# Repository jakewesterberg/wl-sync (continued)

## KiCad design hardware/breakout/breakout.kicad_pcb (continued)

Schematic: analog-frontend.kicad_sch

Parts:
C34, C35, C36, C37, C38, C39, C40, C41, C42, C43, C44, C45, C46, C47, C52, C53, C58, C59, C60, C61, C62, C63, C64, C65, C66, C67, C68, C69, C70, C71: 100nF; C_0603_1608Metric
C48, C50: 22pF; C_0603_1608Metric
C49, C51: 6.8nF; C_0603_1608Metric
C54: 1.2nF; C_0603_1608Metric
C55: 1.0nF; C_0603_1608Metric
C56: 1.5nF; C_0603_1608Metric
C57: 220pF; C_0603_1608Metric
D23, D24, D25, D26, D27, D28, D29, D30, D31, D32, D33, D34, D35, D36, D37, D38: BAT54S; SOT-23
J19: ACCES I/O USB-AO16-8A mating DB37 -- six eye chan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; DSUB-37_Pins_Horizontal_P2.77x2.84mm_EdgePinOffset9.90mm_Ho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
J20: Dual panel BNC: Photodiode 1 (passive, coax, phot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; BNC_Dual_RA_Isolated
J22: Dual panel BNC: Microphone (battery-powered, in b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; BNC_Dual_RA_Isolated
J24: Dual panel BNC: Accelerometer motion energy (batt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; BNC_Dual_RA_Isolated
J26: Dual panel BNC: Joystick Y (battery-powered, in b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; BNC_Dual_RA_Isolated
J28: Misc analog input 1 (panel BNC, /1//2 selectable)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; PinHeader_2x03_P2.54mm_Vertical
J29: Dual panel BNC: Misc analog input 2 (panel BNC, /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; BNC_Dual_RA_Isolated
J30: Misc analog input 2 (panel BNC, /1//2 selectable)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; PinHeader_2x03_P2.54mm_Vertical
J32: Misc analog input 3 (panel BNC, /1//2 selectable)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; PinHeader_2x03_P2.54mm_Vertical
R27, R35, R37, R43, R53, R55, R57, R59, R61, R67, R73: 10; R_0603_1608Metric
R28, R29, R30, R31, R32, R33, R34, R36, R42, R52, R54, R56, R58, R60, R66, R72: 1k; R_0603_1608Metric
R38, R40: 180k; R_0603_1608Metric
R39, R41: 1.6k; R_0603_1608Metric
R44, R45, R46, R47, R62, R63, R64, R65, R68, R69, R70, R71, R74, R75, R76, R77: 10.0k 0.1%; R_0603_1608Metric
R48, R49: 12.1k; R_0603_1608Metric
R50, R51: 23.2k; R_0603_1608Metric
R196, R197: DNP; R_0603_1608Metric; not fitted
U16, U17, U18, U19, U20, U21, U24, U25, U26, U27, U28, U29, U30: INA105KU; SOIC-8_3.9x4.9mm_P1.27mm
U22: OPA2197IDR; SOIC-8_3.9x4.9mm_P1.27mm
U23: OPA4197IDR; SOIC-14_3.9x8.7mm_P1.27mm

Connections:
ACCESIO_AGND: J19.1 (AGND), J19.2 (AGND), J19.3 (AGND), J19.4 (AGND), J19.5 (AGND), J19.6 (AGND), J19.7 (AGND), J19.8 (AGND), J19.9 (AGND), J19.10 (AGND), J19.11 (AGND), J19.12 (AGND), J19.13 (AGND), J19.14 (AGND), J19.15 (AGND), J19.16 (AGND), J19.17 (AGND), J19.18 (AGND), J19.19 (AGND), R27.1, U16.2 (-), U17.2 (-), U18.2 (-), U19.2 (-), U20.2 (-), U21.2 (-)
ACCESIO_SHELL: J19.SH; also elsewhere on the board
A_ACC: U25.5 (SENSE), U25.6; also elsewhere on the board
A_ACC_CLAMP: D33.3 (COM), R54.2, U25.3 (+)
A_ACC_RAW: J24.1 (A_In), R54.1
A_ACC_SHLD: J24.2 (A_Ext), R55.1, U25.2 (-)
A_AMB: U24.5 (SENSE), U24.6; also elsewhere on the board
A_AMB_CLAMP: D32.3 (COM), R52.2, U24.3 (+)
A_AMB_RAW: J22.3 (B_In), R52.1
A_AMB_SHLD: J22.4 (B_Ext), R53.1, U24.2 (-)
A_EYE_LP: U20.5 (SENSE), U20.6; also elsewhere on the board
A_EYE_LP_CLAMP: D27.3 (COM), R32.2, U20.3 (+)
A_EYE_LP_DAC: J19.24 (DAC4), R32.1
A_EYE_LX: U16.5 (SENSE), U16.6; also elsewhere on the board
A_EYE_LX_CLAMP: D23.3 (COM), R28.2, U16.3 (+)
A_EYE_LX_DAC: J19.20 (DAC0), R28.1
A_EYE_LY: U17.5 (SENSE), U17.6; also elsewhere on the board
A_EYE_LY_CLAMP: D24.3 (COM), R29.2, U17.3 (+)
A_EYE_LY_DAC: J19.21 (DAC1), R29.1
A_EYE_RP: U21.5 (SENSE), U21.6; also elsewhere on the board
A_EYE_RP_CLAMP: D28.3 (COM), R33.2, U21.3 (+)
A_EYE_RP_DAC: J19.25 (DAC5), R33.1
A_EYE_RX: U18.5 (SENSE), U18.6; also elsewhere on the board
A_EYE_RX_CLAMP: D25.3 (COM), R30.2, U18.3 (+)
A_EYE_RX_DAC: J19.22 (DAC2), R30.1
A_EYE_RY: U19.5 (SENSE), U19.6; also elsewhere on the board
A_EYE_RY_CLAMP: D26.3 (COM), R31.2, U19.3 (+)
A_EYE_RY_DAC: J19.23 (DAC3), R31.1
A_JOY_X: U26.5 (SENSE), U26.6; also elsewhere on the board
A_JOY_X_CLAMP: D34.3 (COM), R56.2, U26.3 (+)
A_JOY_X_RAW: J24.3 (B_In), R56.1
A_JOY_X_SHLD: J24.4 (B_Ext), R57.1, U26.2 (-)
A_JOY_Y: U27.5 (SENSE), U27.6; also elsewhere on the board
A_JOY_Y_CLAMP: D35.3 (COM), R58.2, U27.3 (+)
A_JOY_Y_RAW: J26.1 (A_In), R58.1
A_JOY_Y_SHLD: J26.2 (A_Ext), R59.1, U27.2 (-)
A_MIC: C56.2, U23.8, U23.9 (-); also elsewhere on the board
A_MIC_CLAMP: D31.3 (COM), R42.2, R44.1
A_MIC_DA: R45.2, R48.1, U23.1
A_MIC_DAN: R44.2, R45.1, U23.2 (-)
A_MIC_DAP: R46.2, R47.1, U23.3 (+)
A_MIC_RAW: J22.1 (A_In), R42.1
A_MIC_S1: C54.2, R50.1, U23.6 (-), U23.7
A_MIC_S1_SKN: C54.1, R48.2, R49.1
A_MIC_S1_SKP: C55.1, R49.2, U23.5 (+)
A_MIC_SHLD: J22.2 (A_Ext), R43.1, R46.1
A_MIC_SKN: C56.1, R50.2, R51.1
A_MIC_SKP: C57.1, R51.2, U23.10 (+)
A_MIC_SPARE_FB: U23.13 (-), U23.14
A_MISC1: U28.5 (SENSE), U28.6; also elsewhere on the board
A_MISC1_CLAMP: D36.3 (COM), J28.1, R60.2, R62.1
A_MISC1_DIV: J28.3, U28.3 (+)
A_MISC1_MID: J28.5, R62.2, R63.1
A_MISC1_RAW: J26.3 (B_In), R60.1
A_MISC1_SHLD: J26.4 (B_Ext), J28.2, R61.1, R64.1
A_MISC1_SHLD_DIV: J28.4, U28.2 (-)
A_MISC1_SHLD_MID: J28.6, R64.2, R65.1
A_MISC2: U29.5 (SENSE), U29.6; also elsewhere on the board
A_MISC2_CLAMP: D37.3 (COM), J30.1, R66.2, R68.1
A_MISC2_DIV: J30.3, U29.3 (+)
A_MISC2_MID: J30.5, R68.2, R69.1
A_MISC2_RAW: J29.1 (A_In), R66.1
A_MISC2_SHLD: J29.2 (A_Ext), J30.2, R67.1, R70.1
A_MISC2_SHLD_DIV: J30.4, U29.2 (-)
A_MISC2_SHLD_MID: J30.6, R70.2, R71.1
A_MISC3: U30.5 (SENSE), U30.6; also elsewhere on the board
A_MISC3_CLAMP: D38.3 (COM), J32.1, R72.2, R74.1
A_MISC3_DIV: J32.3, U30.3 (+)
A_MISC3_MID: J32.5, R74.2, R75.1
A_MISC3_RAW: J29.3 (B_In), R72.1
A_MISC3_SHLD: J29.4 (B_Ext), J32.2, R73.1, R76.1
A_MISC3_SHLD_DIV: J32.4, U30.2 (-)
A_MISC3_SHLD_MID: J32.6, R76.2, R77.1
A_PD1: C49.1, R39.2; also elsewhere on the board
A_PD1_CLAMP: C48.2, D29.3 (COM), R34.2, R38.2, R196.2, U22.2 (-)
A_PD1_RAW: J20.1 (A_In), R34.1
A_PD1_RAWOUT: C48.1, R38.1, R39.1, R196.1, U22.1
A_PD1_SHLD: J20.2 (A_Ext), R35.1, U22.3 (+)
A_PD2: C51.1, R41.2; also elsewhere on the board
A_PD2_CLAMP: C50.2, D30.3 (COM), R36.2, R40.2, R197.2, U22.6 (-)
A_PD2_RAW: J20.3 (B_In), R36.1
A_PD2_RAWOUT: C50.1, R40.1, R41.1, R197.1, U22.7
A_PD2_SHLD: J20.4 (B_Ext), R37.1, U22.5 (+)

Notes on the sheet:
Analog front end (Task 10a) -- 16 sources, every one received DIFFERENTIALLY.
Consumes +12V/-12V/AGND (Task 7). Produces the 16 A_* nets below; Tasks 10b/10c/
10d (NI fan-out, mux+Intan diff-amps, comparators) consume them by this same
global-label name -- neither exists yet, but each net's own driving stage
already puts 2 pins on it (SENSE=OUTPUT / filter R+C midpoint / SK follower
feedback), so kicad-cli sch erc's isolated_pin_label check does not fire here
even without a downstream load -- see check_breakout_analog_frontend_netlist.py
and task-10a-report.md for the full ERC accounting.
WHY DIFFERENTIAL (spec Sec.5.6): the rig sits in a Faraday cage sound booth.
Sensors inside are battery powered so no mains conductor crosses the cage wall --
only signal, through a BNC shield. Whether the bulkhead bonds that shield to the
cage shell is UNDECIDED. If it does, circulating current in the shield (which is
also the signal return) would add straight onto the signal through a plain AGND-
referenced buffer. The shield cannot simply be lifted -- it IS the return path.
So every front end senses centre against shield AT THE CONNECTOR and a difference
amplifier turns the disturbance into common mode instead. This is what lets the
bulkhead decision be made, or reversed, later, without touching this board.
The six ACCESIO eye channels get the identical treatment against the ACCESIO's
own AGND pins (bonded to board AGND through ~10R, same as a BNC shell) -- it sits
on a separately-earthed eye-tracker PC, the same class of ground offset.
Common front end, every one of the 16 sources: isolated BNC (or ACCESIO DB37
pin) -> 1k series -> BAT54S clamp to +12V/-12V (protects the receiving op-amp's
own supply rails) -> source-specific back half below.
13 of 16 (6 ACCESIO eyes, ambient, accelerometer, joystick X/Y, misc x3): one
INA105KU per channel -- TI's monolithic precision unity-gain difference
amplifier (matched internal resistor network, REF pin lands the output on AGND
regardless of what the shield/ACCESIO_AGND reference is doing). Named
'INA134-class' in the brief; INA134 itself has no stock KiCad symbol and is an
audio-specific part -- INA105 fills the identical topological role and is a
real, current, hand-solderable TI part (same Value-substitution discipline as
the mule's SN74LVC541APW-on-74LS541-symbol precedent, hardware/README.md).
Photodiodes (A_PD1/A_PD2, spec Sec.6.3.1): PASSIVE, so the input stage is a
transimpedance amplifier, not a difference amp. Photodiode lives at the remote
sensor (not on this board, like the mic/accelerometer/joystick) -- cathode on
the coax centre (TIA summing junction, op-amp '-'), anode on the shield.
Non-inverting input ('+') is referenced to the LOCAL SHIELD, not AGND: feedback
forces the summing junction to track '+', so both photodiode terminals sit at
the shield's own local potential at every instant -- true photovoltaic (zero-
bias) operation survives a shield disturbance instead of that disturbance
appearing as a real bias voltage across the diode.

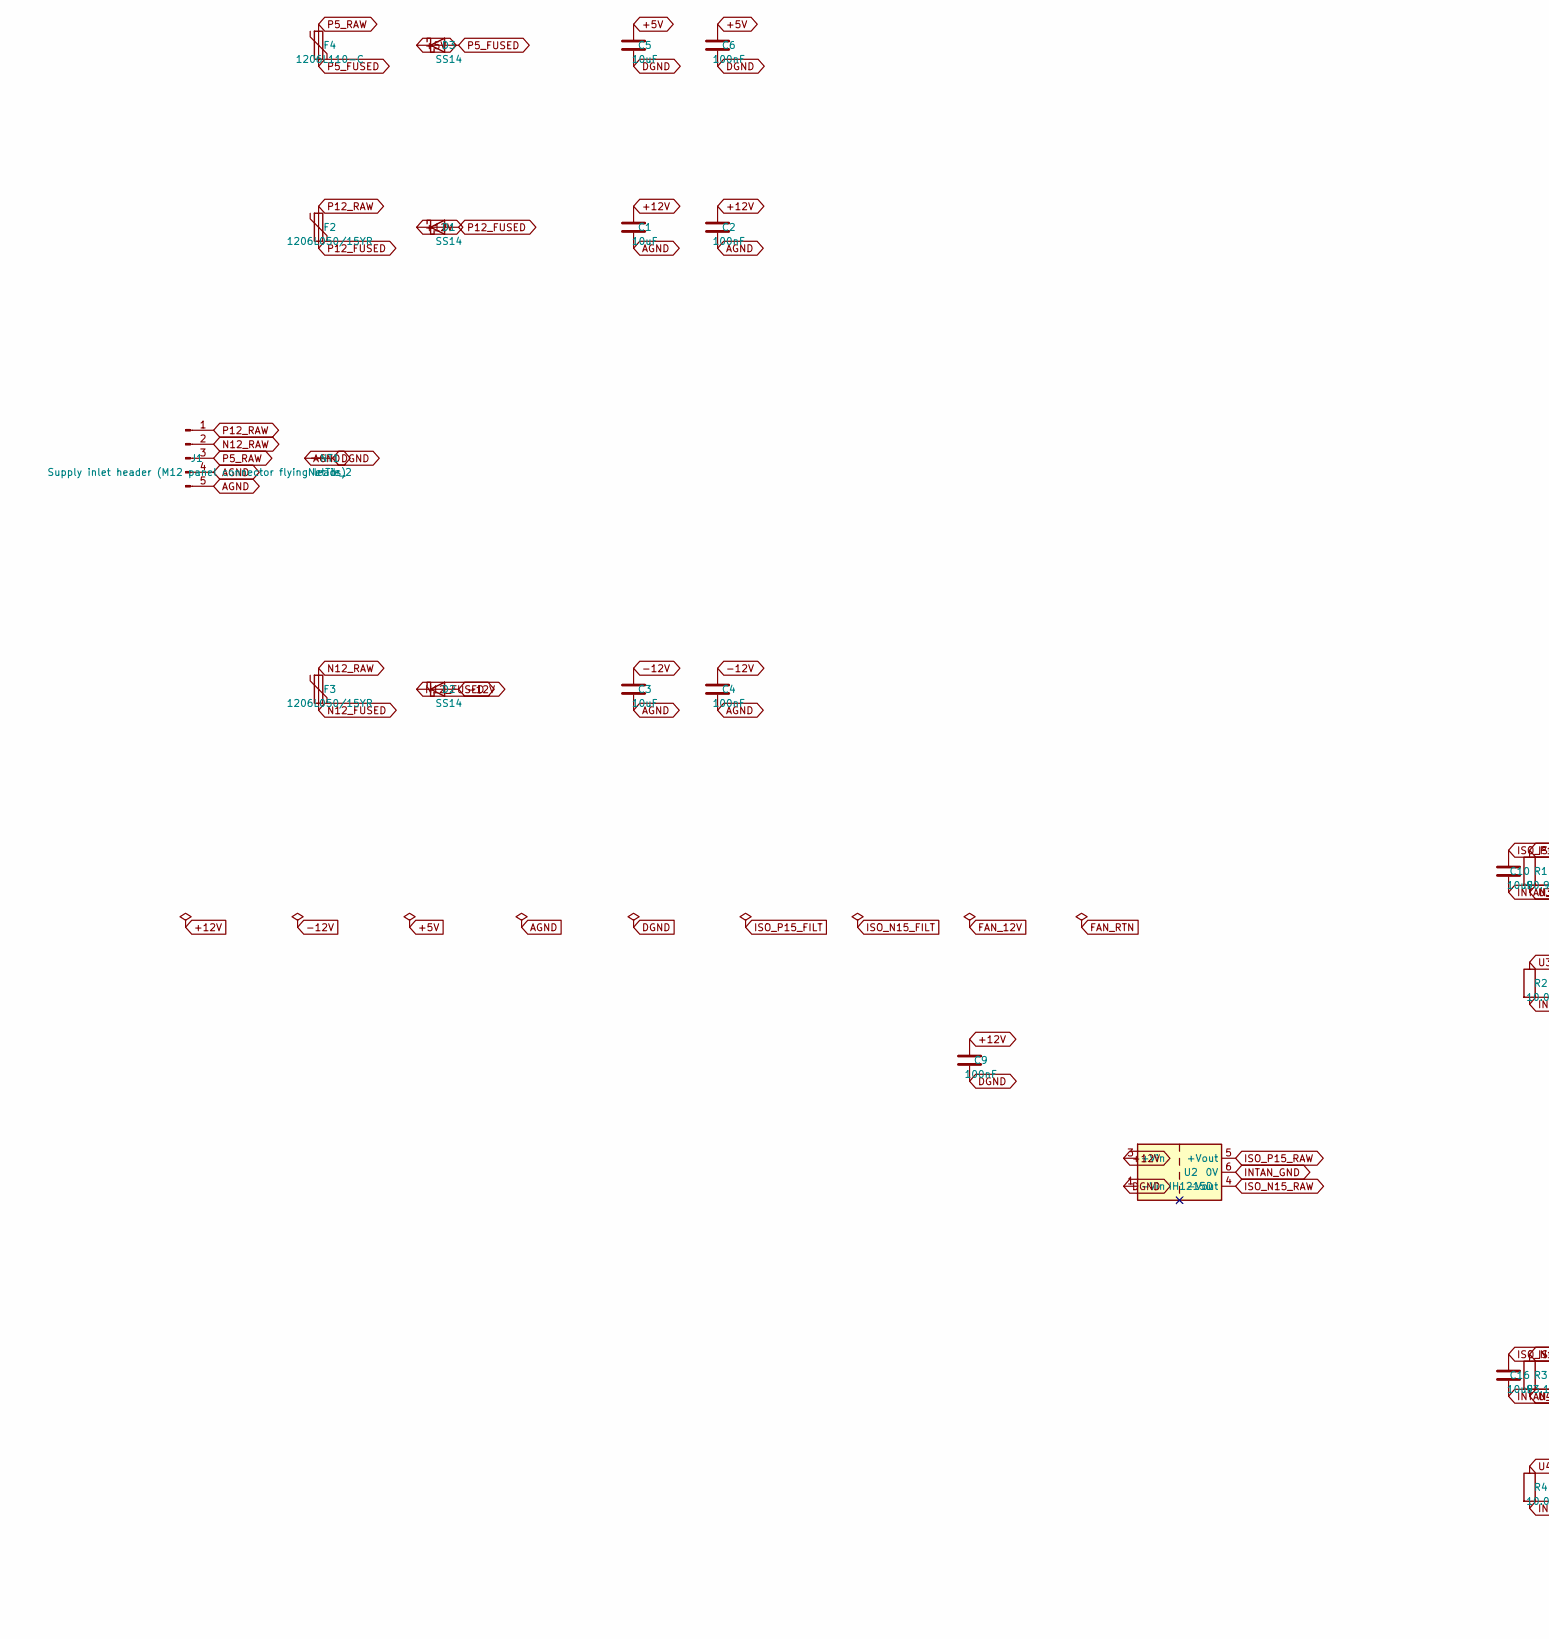
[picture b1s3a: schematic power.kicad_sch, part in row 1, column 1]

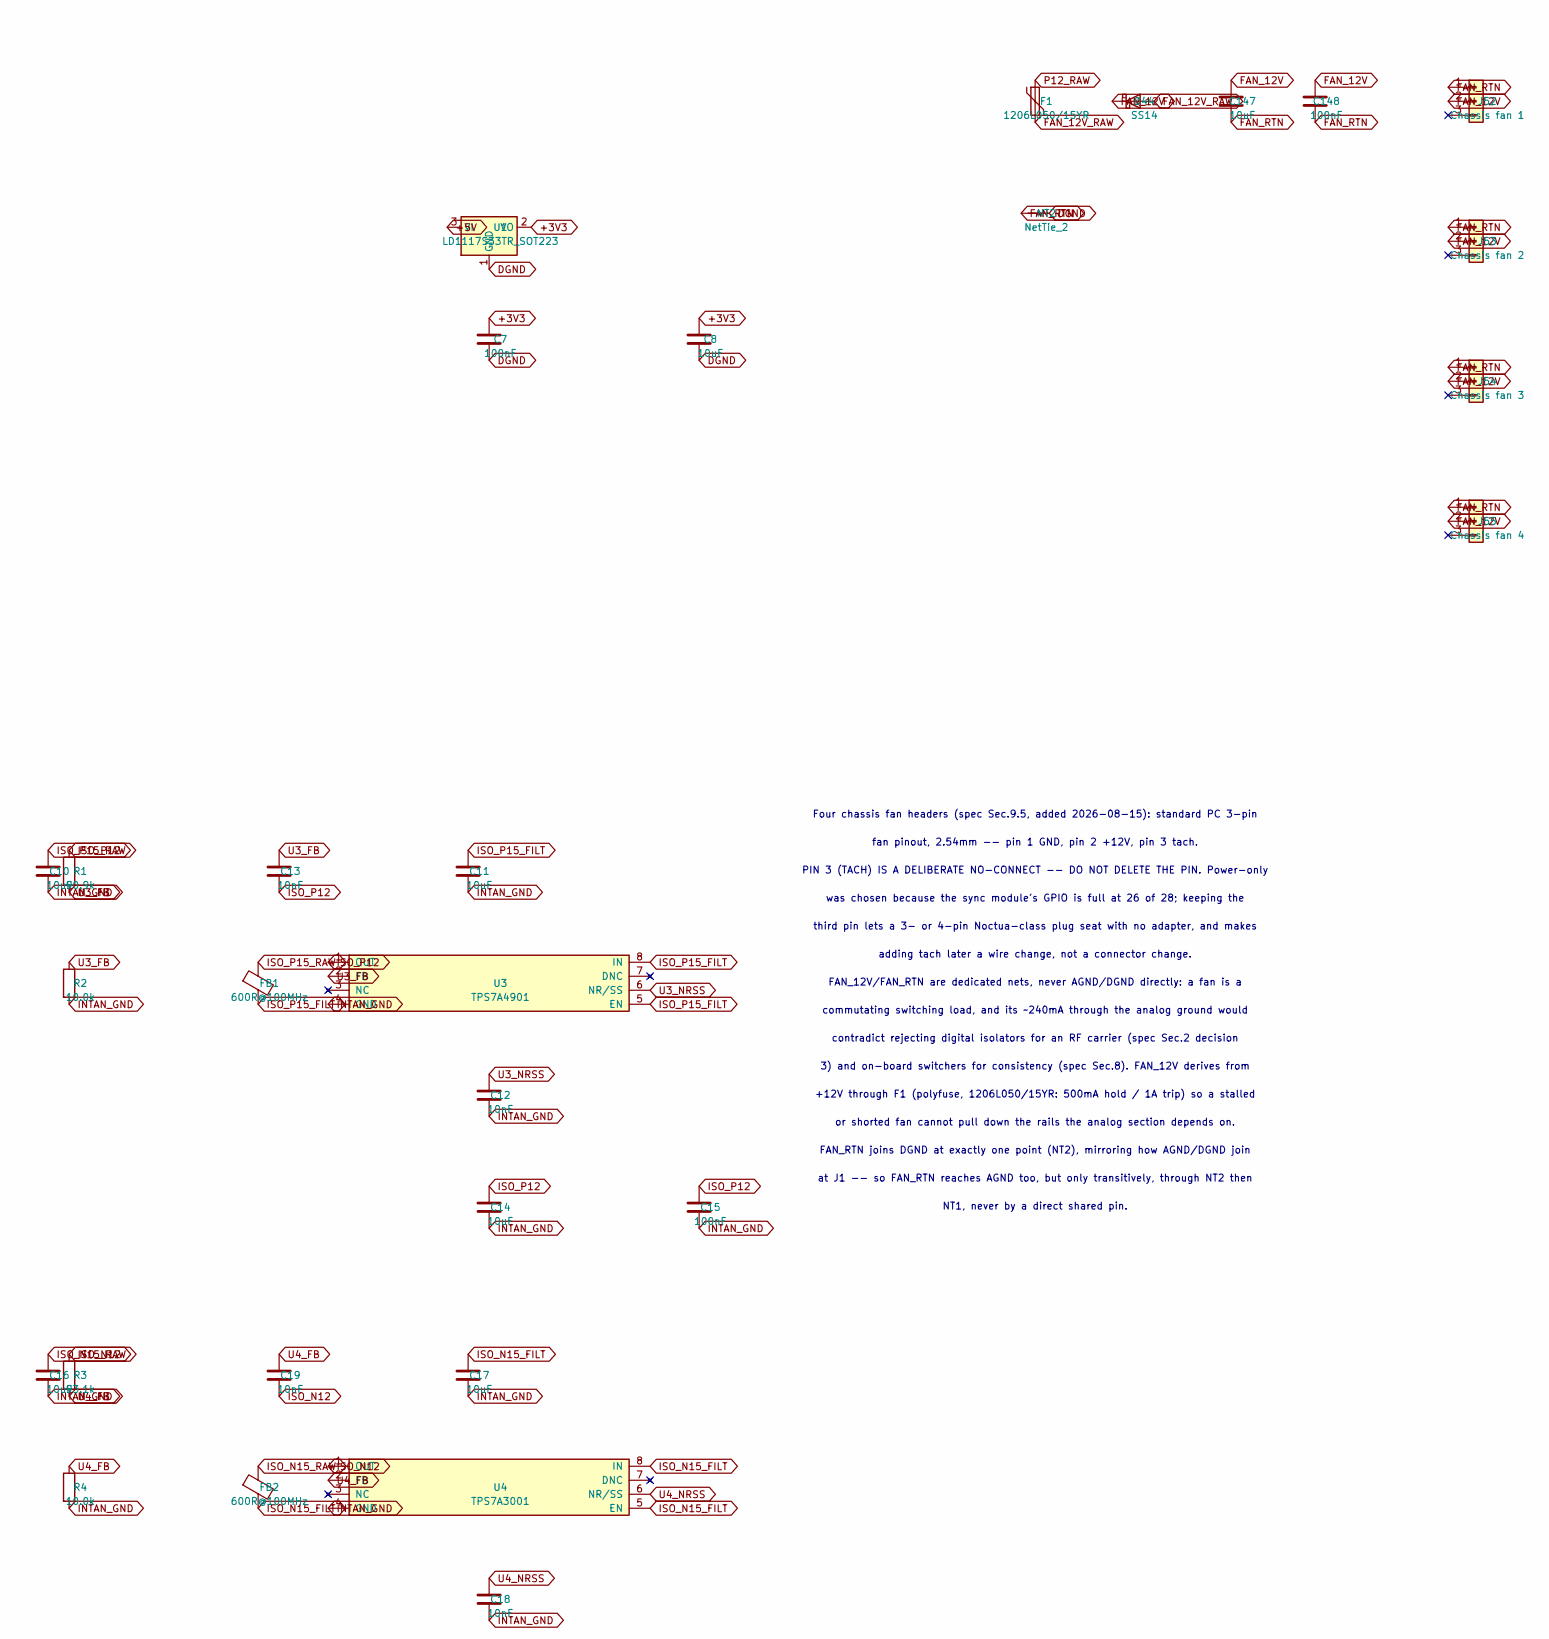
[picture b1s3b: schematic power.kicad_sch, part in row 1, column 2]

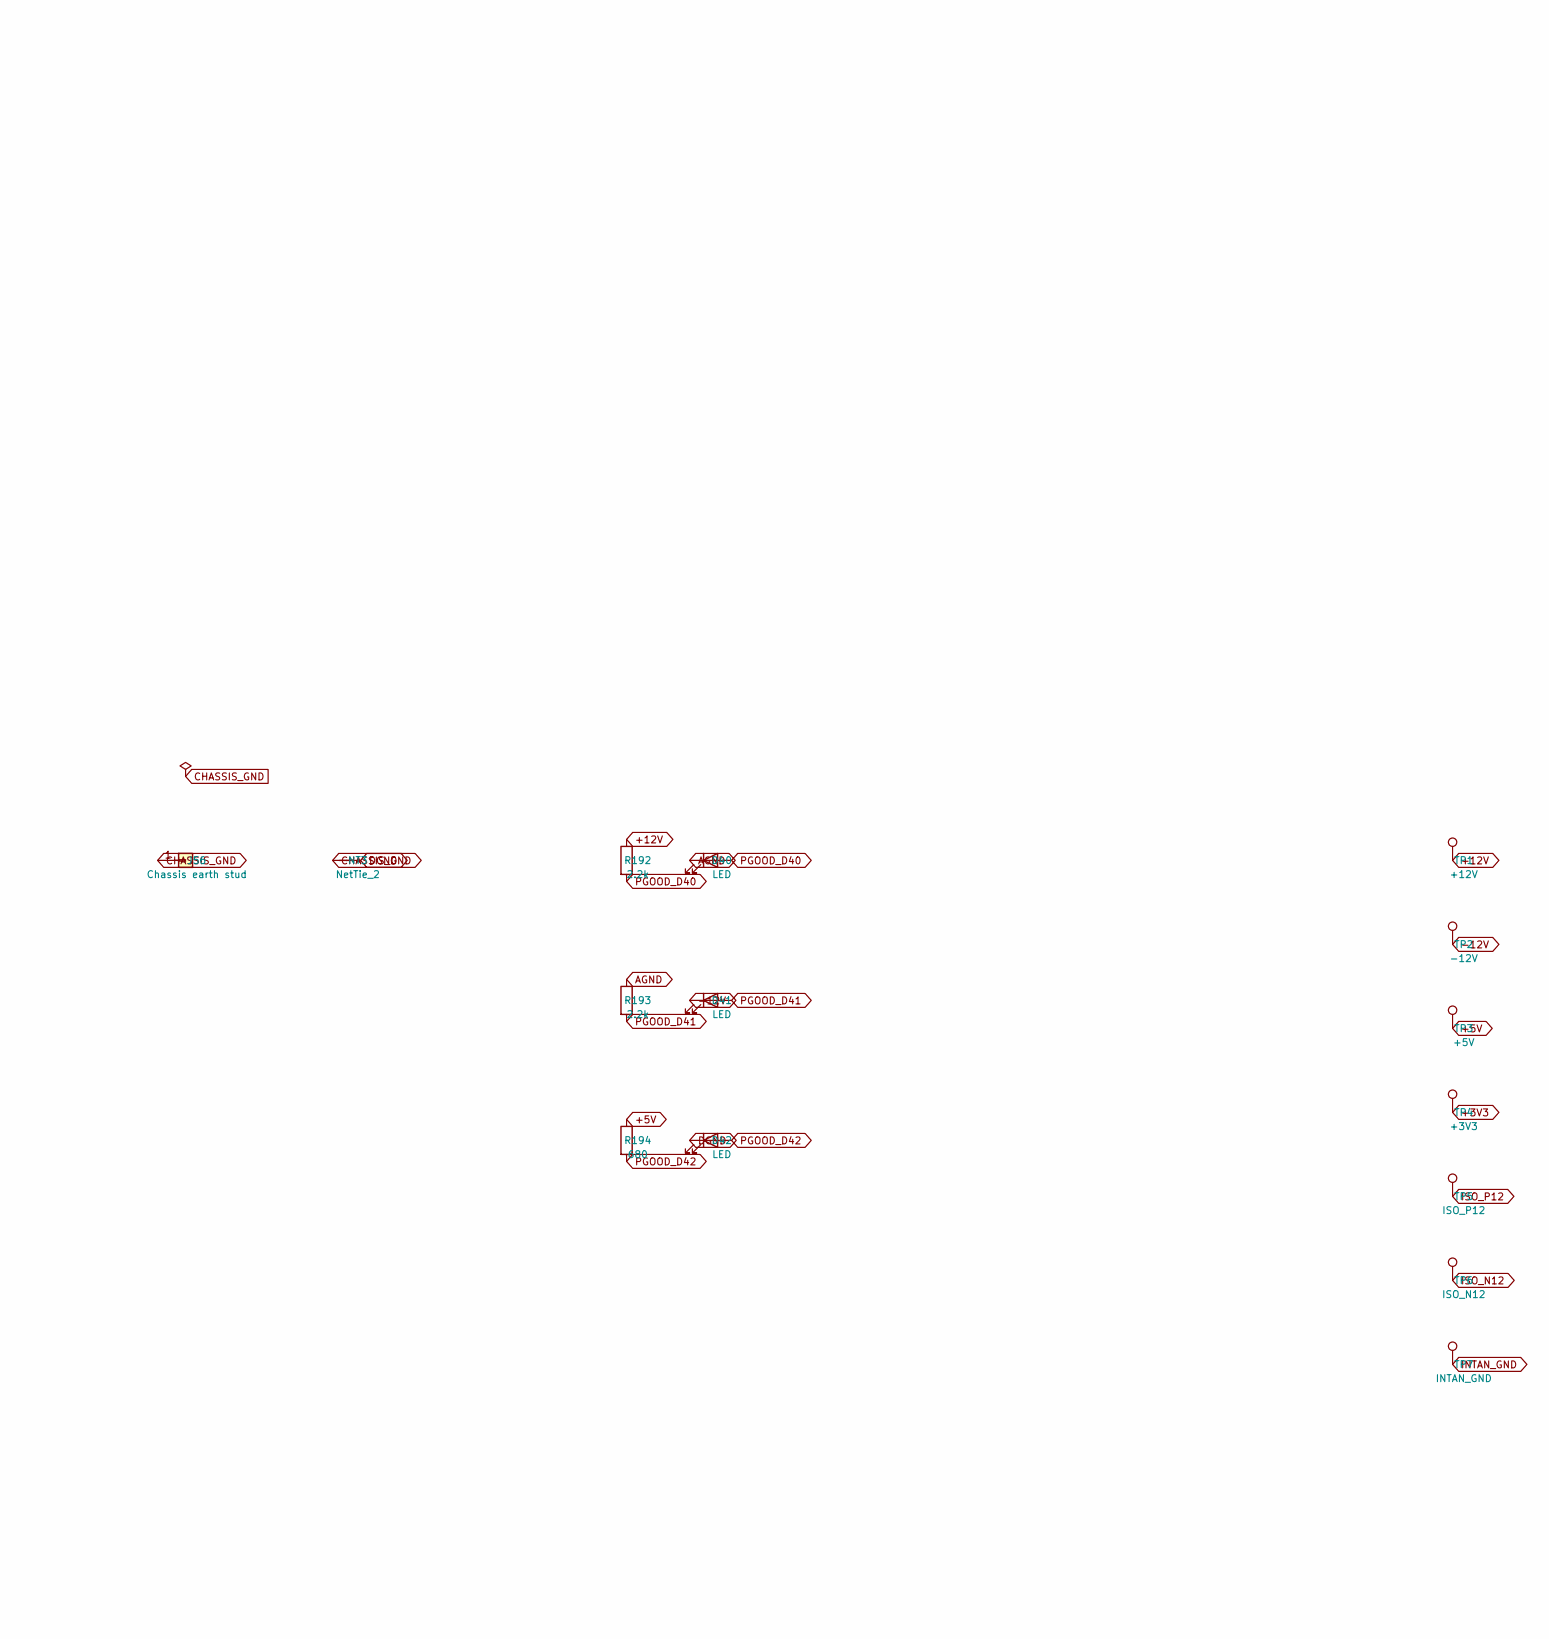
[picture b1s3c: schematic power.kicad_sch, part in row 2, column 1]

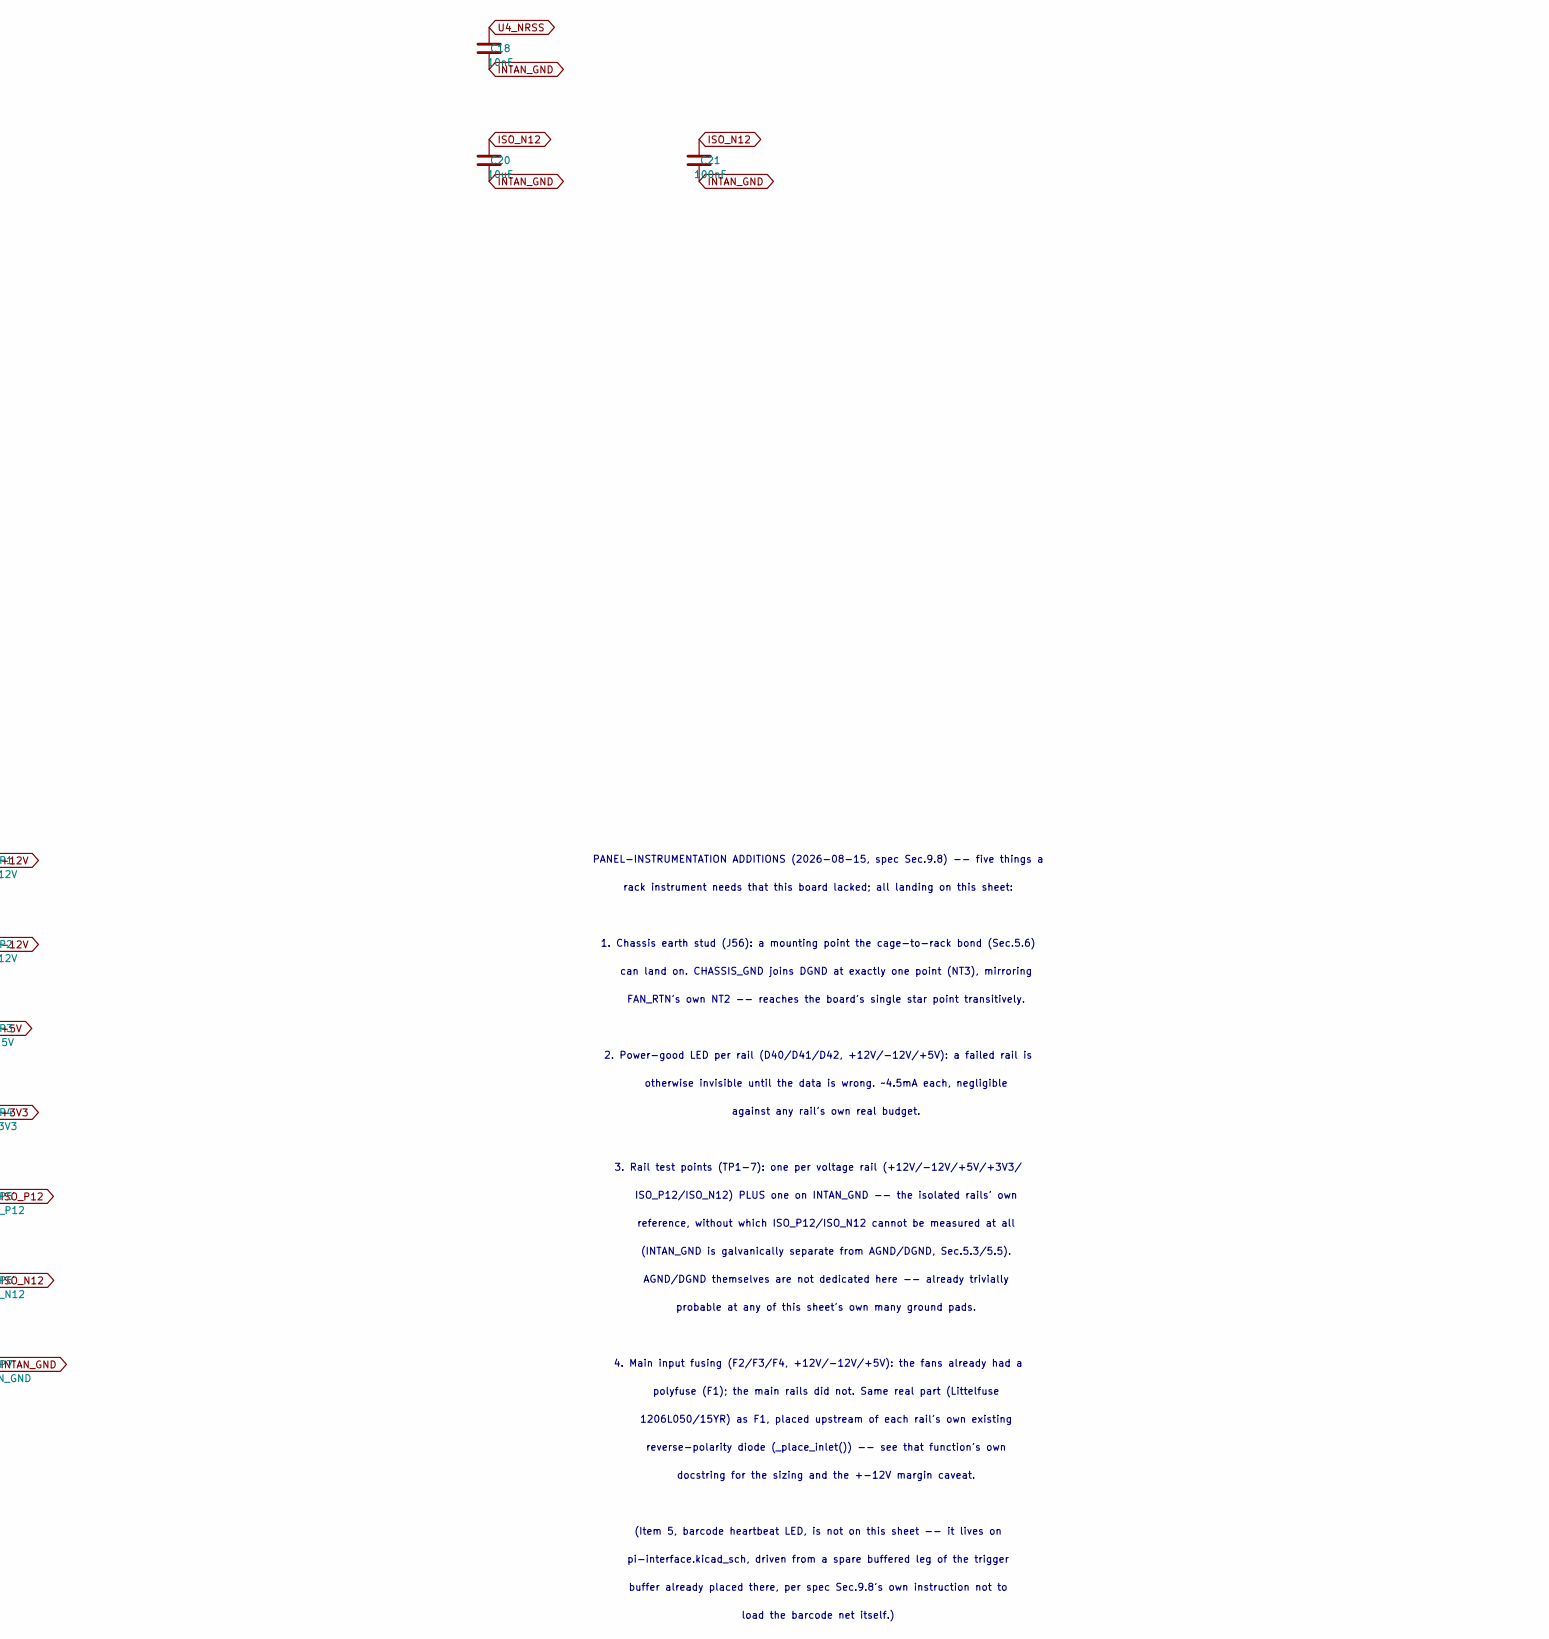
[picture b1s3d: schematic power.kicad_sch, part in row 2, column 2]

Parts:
C1, C3, C5, C8, C10, C11, C14, C16, C17, C20, C147: 10uF; C_0805_2012Metric
C2, C4, C6, C7, C9, C15, C21, C148: 100nF; C_0603_1608Metric
C12, C13, C18, C19: 10nF; C_0603_1608Metric
D1, D2, D3, D44: SS14; D_SMA_Handsoldering
D40, D41, D42: LED; LED_0603_1608Metric_Pad1.05x0.95mm_HandSolder
F1, F2, F3: 1206L050/15YR; Fuse_1206_3216Metric_Pad1.42x1.75mm_HandSolder
F4: 1206L110-C; Fuse_1206_3216Metric_Pad1.42x1.75mm_HandSolder
FB1, FB2: 600R@100MHz; L_0805_2012Metric_Pad1.05x1.20mm_HandSolder
J1: Supply inlet header (M12 panel connector flying l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; PinHeader_1x05_P2.54mm_Vertical
J52: Chassis fan 1; PinHeader_1x03_P2.54mm_Vertical
J53: Chassis fan 2; PinHeader_1x03_P2.54mm_Vertical
J54: Chassis fan 3; PinHeader_1x03_P2.54mm_Vertical
J55: Chassis fan 4; PinHeader_1x03_P2.54mm_Vertical
J56: Chassis earth stud; MountingHole_3.2mm_M3_Pad
NT1, NT2, NT3: NetTie_2; NetTie-2_SMD_Pad2.0mm
R1: 90.9k; R_0603_1608Metric
R2, R4: 10.0k; R_0603_1608Metric
R3: 93.1k; R_0603_1608Metric
R192, R193: 2.2k; R_0603_1608Metric
R194: 680; R_0603_1608Metric
TP1: +12V; TestPoint_THTPad_2.0x2.0mm_Drill1.0mm
TP2: -12V; TestPoint_THTPad_2.0x2.0mm_Drill1.0mm
TP3: +5V; TestPoint_THTPad_2.0x2.0mm_Drill1.0mm
TP4: +3V3; TestPoint_THTPad_2.0x2.0mm_Drill1.0mm
TP5: ISO_P12; TestPoint_THTPad_2.0x2.0mm_Drill1.0mm
TP6: ISO_N12; TestPoint_THTPad_2.0x2.0mm_Drill1.0mm
TP7: INTAN_GND; TestPoint_THTPad_2.0x2.0mm_Drill1.0mm
U1: LD1117S33TR_SOT223; SOT-223-3_TabPin2
U2: IH1215D; Converter_DCDC_XP_POWER-IHxxxxD_THT
U3: TPS7A4901; HVSSOP-8-1EP_3x3mm_P0.65mm_EP1.57x1.89mm
U4: TPS7A3001; HVSSOP-8-1EP_3x3mm_P0.65mm_EP1.57x1.89mm

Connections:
+3V3: C7.1, C8.1, TP4.1, U1.2 (VO); also elsewhere on the board
FAN_12V_RAW: D44.2 (A), F1.2
INTAN_GND: C10.2, C11.2, C12.2, C14.2, C15.2, C16.2, C17.2, C18.2, C20.2, C21.2, R2.2, R4.2, TP7.1, U2.6 (0V), U3.4 (GND), U3.9, U4.4 (GND), U4.9; also elsewhere on the board
ISO_N12: C19.2, C20.1, C21.1, R3.1, TP6.1, U4.1 (OUT); also elsewhere on the board
ISO_N15_RAW: C16.1, FB2.1, U2.4 (-Vout)
ISO_P12: C13.2, C14.1, C15.1, R1.1, TP5.1, U3.1 (OUT); also elsewhere on the board
ISO_P15_RAW: C10.1, FB1.1, U2.5 (+Vout)
N12_FUSED: D2.1 (K), F3.2
N12_RAW: F3.1, J1.2
P5_FUSED: D3.2 (A), F4.2
P5_RAW: F4.1, J1.3
P12_FUSED: D1.2 (A), F2.2
P12_RAW: F1.1, F2.1, J1.1
PGOOD_D40: D40.2 (A), R192.2
PGOOD_D41: D41.2 (A), R193.2
PGOOD_D42: D42.2 (A), R194.2
U3_FB: C13.1, R1.2, R2.1, U3.2 (FB)
U3_NRSS: C12.1, U3.6 (NR/SS)
U4_FB: C19.1, R3.2, R4.1, U4.2 (FB)
U4_NRSS: C18.1, U4.6 (NR/SS)

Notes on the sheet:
Four chassis fan headers (spec Sec.9.5, added 2026-08-15): standard PC 3-pin
fan pinout, 2.54mm -- pin 1 GND, pin 2 +12V, pin 3 tach.
PIN 3 (TACH) IS A DELIBERATE NO-CONNECT -- DO NOT DELETE THE PIN. Power-only
was chosen because the sync module's GPIO is full at 26 of 28; keeping the
third pin lets a 3- or 4-pin Noctua-class plug seat with no adapter, and makes
adding tach later a wire change, not a connector change.
FAN_12V/FAN_RTN are dedicated nets, never AGND/DGND directly: a fan is a
commutating switching load, and its ~240mA through the analog ground would
contradict rejecting digital isolators for an RF carrier (spec Sec.2 decision
3) and on-board switchers for consistency (spec Sec.8). FAN_12V derives from
+12V through F1 (polyfuse, 1206L050/15YR: 500mA hold / 1A trip) so a stalled
or shorted fan cannot pull down the rails the analog section depends on.
FAN_RTN joins DGND at exactly one point (NT2), mirroring how AGND/DGND join
at J1 -- so FAN_RTN reaches AGND too, but only transitively, through NT2 then
NT1, never by a direct shared pin.
PANEL-INSTRUMENTATION ADDITIONS (2026-08-15, spec Sec.9.8) -- five things a
rack instrument needs that this board lacked; all landing on this sheet:
1. Chassis earth stud (J56): a mounting point the cage-to-rack bond (Sec.5.6)
can land on. CHASSIS_GND joins DGND at exactly one point (NT3), mirroring
FAN_RTN's own NT2 -- reaches the board's single star point transitively.
2. Power-good LED per rail (D40/D41/D42, +12V/-12V/+5V): a failed rail is
otherwise invisible until the data is wrong. ~4.5mA each, negligible
against any rail's own real budget.
3. Rail test points (TP1-7): one per voltage rail (+12V/-12V/+5V/+3V3/
ISO_P12/ISO_N12) PLUS one on INTAN_GND -- the isolated rails' own
reference, without which ISO_P12/ISO_N12 cannot be measured at all
(INTAN_GND is galvanically separate from AGND/DGND, Sec.5.3/5.5).
AGND/DGND themselves are not dedicated here -- already trivially
probable at any of this sheet's own many ground pads.
4. Main input fusing (F2/F3/F4, +12V/-12V/+5V): the fans already had a
polyfuse (F1); the main rails did not. Same real part (Littelfuse
1206L050/15YR) as F1, placed upstream of each rail's own existing
reverse-polarity diode (_place_inlet()) -- see that function's own
docstring for the sizing and the +-12V margin caveat.
(Item 5, barcode heartbeat LED, is not on this sheet -- it lives on
pi-interface.kicad_sch, driven from a spare buffered leg of the trigger
buffer already placed there, per spec Sec.9.8's own instruction not to
load the barcode net itself.)
